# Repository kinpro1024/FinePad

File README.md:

# FinePad (kinpro1024 × ROY21)
### Precision Dual-Axis Macropad
FinePad is a macropad designed with fine pointer control for precision-requiring situations like colour curve modificatioins or timeline scrubbing.
FinePad comes with two independently scrolling Rotary Encoder Knobs for precision X and Y axis control of the Pointer.

This is the version of finepad with no screen. A version with mode toggle and screen is coming soon.

Finepad is built on a Custom PCB.

*This is a concept sketch of the FinePad.*

## Why Fine pointer control
A macropad with dual fine scrolling knobs for X and Y control gives users a level of precision that mice and trackpads struggle to achieve. When working with:
- Colour Curves
- Exposure
- Fine Parameter Sliders
As even small unintended movements with a mouse can lead to inconsistent results in these situations.

**Dedicated knobs allow for smooth, incremental control, making subtle adjustments far more intuitive and repeatable.** Separating X and Y into physical controls also reduces cognitive load, since each axis becomes a deliberate action rather than a coordinated hand movement. This is especially valuable in workflows like:
- Photo Editing
- Colour Grading
- Audio Tuning
Where precision directly impacts output quality. Overall, it transforms delicate adjustments from a frustrating task into a controlled, tactile experience.

## Hardware Overview
FinePad uses a custom PCB as it's base:
- Raspberry Pi Pico handles Firmware.
- Two AS5600 Hall Effect Absolute Encoders.

# FinePad (screenless) was completed on 10/Apr/2026. It is a collaboration between kinpro1024 and ROY21.
# FinePad will get a toggle switch, screen and volume knob in an upcoming update. The full firmware will also come soon.

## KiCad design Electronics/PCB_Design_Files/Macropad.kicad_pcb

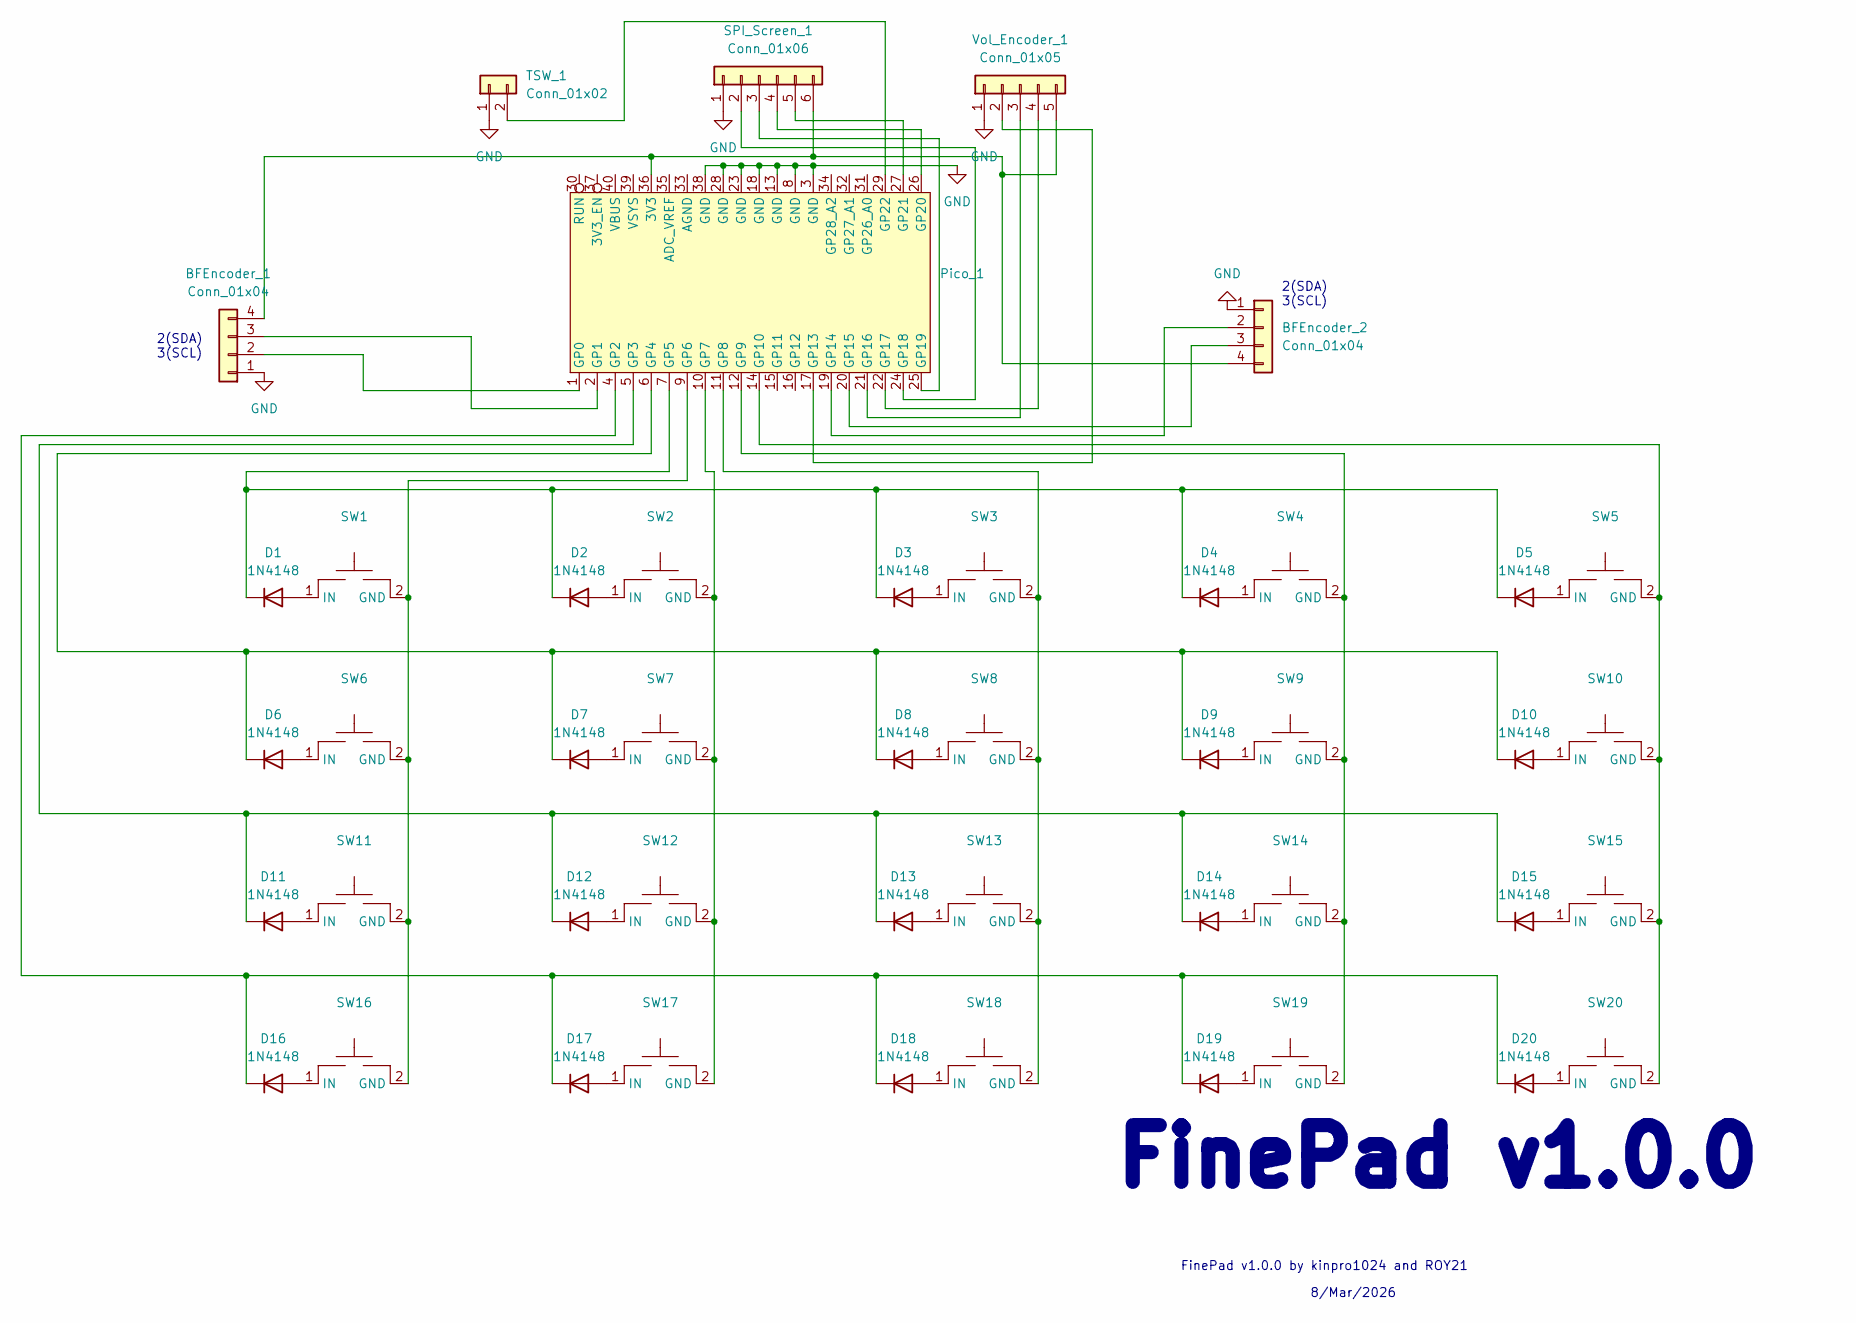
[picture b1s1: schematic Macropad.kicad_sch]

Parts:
BFEncoder_1, BFEncoder_2: Conn_01x04; JST_XH_S4B-XH-A-1_1x04_P2.50mm_Horizontal
D1, D2, D3, D4, D5, D6, D7, D8, D9, D10, D11, D12, D13, D14, D15, D16, D17, D18, D19, D20: 1N4148; D_DO-35_SOD27_P7.62mm_Horizontal
Pico_1: Pico_SMT
SPI_Screen_1: Conn_01x06; JST_XH_S6B-XH-A-1_1x06_P2.50mm_Horizontal
SW1, SW2, SW3, SW4, SW5, SW6, SW7, SW8, SW9, SW10, SW11, SW12, SW13, SW14, SW15, SW16, SW17, SW18, SW19, SW20: Gateron_G_Pro_3
TSW_1: Conn_01x02; JST_XH_S2B-XH-A-1_1x02_P2.50mm_Horizontal
Vol_Encoder_1: Conn_01x05; JST_XH_S5B-XH-A-1_1x05_P2.50mm_Horizontal

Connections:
GND: BFEncoder_1.1, BFEncoder_2.1, Pico_1.3 (GND), Pico_1.8 (GND), Pico_1.13 (GND), Pico_1.18 (GND), Pico_1.23 (GND), Pico_1.28 (GND), Pico_1.38 (GND), SPI_Screen_1.1, TSW_1.1, Vol_Encoder_1.1; also elsewhere on the board
unnamed 1: BFEncoder_1.2, Pico_1.1 (GP0); also elsewhere on the board
unnamed 2: BFEncoder_1.3, Pico_1.2 (GP1); also elsewhere on the board
unnamed 3: BFEncoder_1.4, BFEncoder_2.4, Pico_1.36 (3V3), SPI_Screen_1.6, Vol_Encoder_1.5; also elsewhere on the board
unnamed 4: BFEncoder_2.2, Pico_1.19 (GP14); also elsewhere on the board
unnamed 5: BFEncoder_2.3, Pico_1.20 (GP15); also elsewhere on the board
unnamed: D1.2 (A), SW1.1 (IN)
unnamed 7: D1.1 (K), D2.1 (K), D3.1 (K), D4.1 (K), D5.1 (K), Pico_1.7 (GP5); also elsewhere on the board
unnamed: D2.2 (A), SW2.1 (IN)
unnamed: D3.2 (A), SW3.1 (IN)
unnamed: D4.2 (A), SW4.1 (IN)
unnamed: D5.2 (A), SW5.1 (IN)
unnamed: D6.2 (A), SW6.1 (IN)
unnamed: D7.2 (A), SW7.1 (IN)
unnamed: D8.2 (A), SW8.1 (IN)
unnamed: D9.2 (A), SW9.1 (IN)
unnamed: D10.2 (A), SW10.1 (IN)
unnamed 17: D6.1 (K), D7.1 (K), D8.1 (K), D9.1 (K), D10.1 (K), Pico_1.6 (GP4); also elsewhere on the board
unnamed: D11.2 (A), SW11.1 (IN)
unnamed 19: D11.1 (K), D12.1 (K), D13.1 (K), D14.1 (K), D15.1 (K), Pico_1.5 (GP3); also elsewhere on the board
unnamed: D12.2 (A), SW12.1 (IN)
unnamed: D13.2 (A), SW13.1 (IN)
unnamed: D14.2 (A), SW14.1 (IN)
unnamed: D15.2 (A), SW15.1 (IN)
unnamed: D16.2 (A), SW16.1 (IN)
unnamed 25: D16.1 (K), D17.1 (K), D18.1 (K), D19.1 (K), D20.1 (K), Pico_1.4 (GP2); also elsewhere on the board
unnamed: D17.2 (A), SW17.1 (IN)
unnamed: D18.2 (A), SW18.1 (IN)
unnamed: D19.2 (A), SW19.1 (IN)
unnamed: D20.2 (A), SW20.1 (IN)
unnamed 30: Pico_1.9 (GP6), SW1.2 (GND), SW6.2 (GND), SW11.2 (GND), SW16.2 (GND); also elsewhere on the board
unnamed 31: Pico_1.10 (GP7), SW2.2 (GND), SW7.2 (GND), SW12.2 (GND), SW17.2 (GND); also elsewhere on the board
unnamed 32: Pico_1.11 (GP8), SW3.2 (GND), SW8.2 (GND), SW13.2 (GND), SW18.2 (GND); also elsewhere on the board
unnamed 33: Pico_1.12 (GP9), SW4.2 (GND), SW9.2 (GND), SW14.2 (GND), SW19.2 (GND); also elsewhere on the board
unnamed 34: Pico_1.14 (GP10), SW5.2 (GND), SW10.2 (GND), SW15.2 (GND), SW20.2 (GND); also elsewhere on the board
unnamed 35: Pico_1.17 (GP13), Vol_Encoder_1.2; also elsewhere on the board
unnamed 36: Pico_1.21 (GP16), Vol_Encoder_1.3; also elsewhere on the board
unnamed 37: Pico_1.22 (GP17), Vol_Encoder_1.4; also elsewhere on the board
unnamed 38: Pico_1.24 (GP18), SPI_Screen_1.2; also elsewhere on the board
unnamed 39: Pico_1.25 (GP19), SPI_Screen_1.3; also elsewhere on the board
unnamed 40: Pico_1.26 (GP20), SPI_Screen_1.4; also elsewhere on the board
unnamed 41: Pico_1.27 (GP21), SPI_Screen_1.5; also elsewhere on the board
unnamed 42: Pico_1.29 (GP22), TSW_1.2; also elsewhere on the board

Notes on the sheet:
FinePad v1.0.0 by kinpro1024 and ROY21
8/Mar/2026
2(SDA) 3(SCL)
FinePad v1.0.0

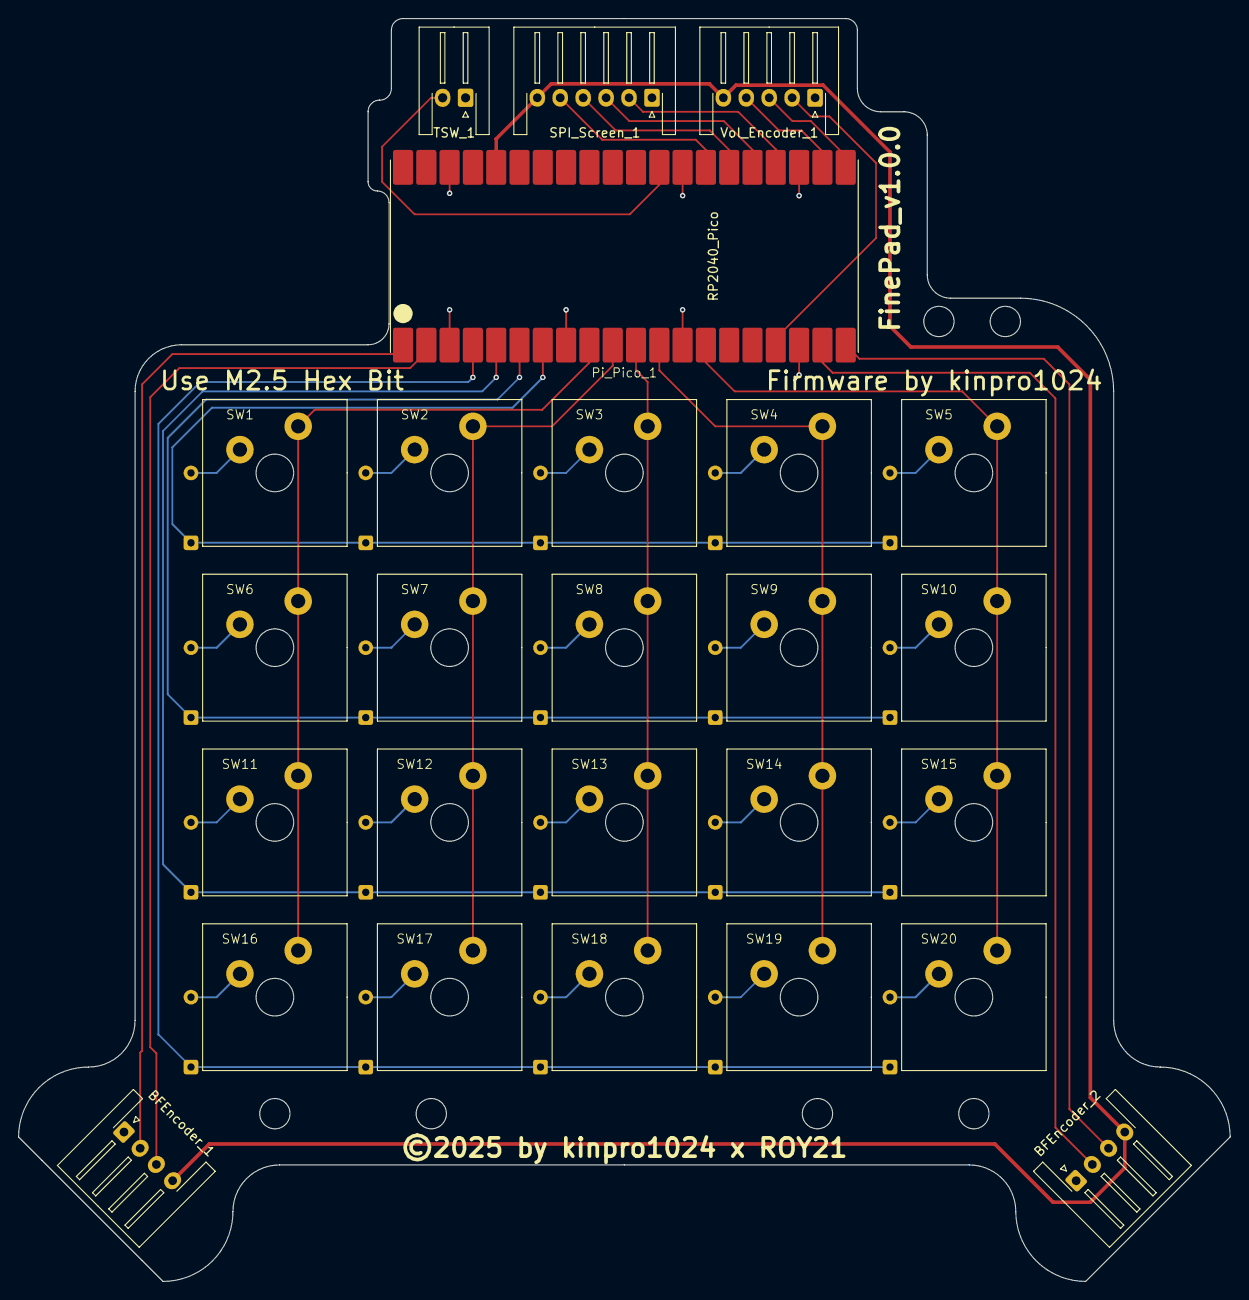
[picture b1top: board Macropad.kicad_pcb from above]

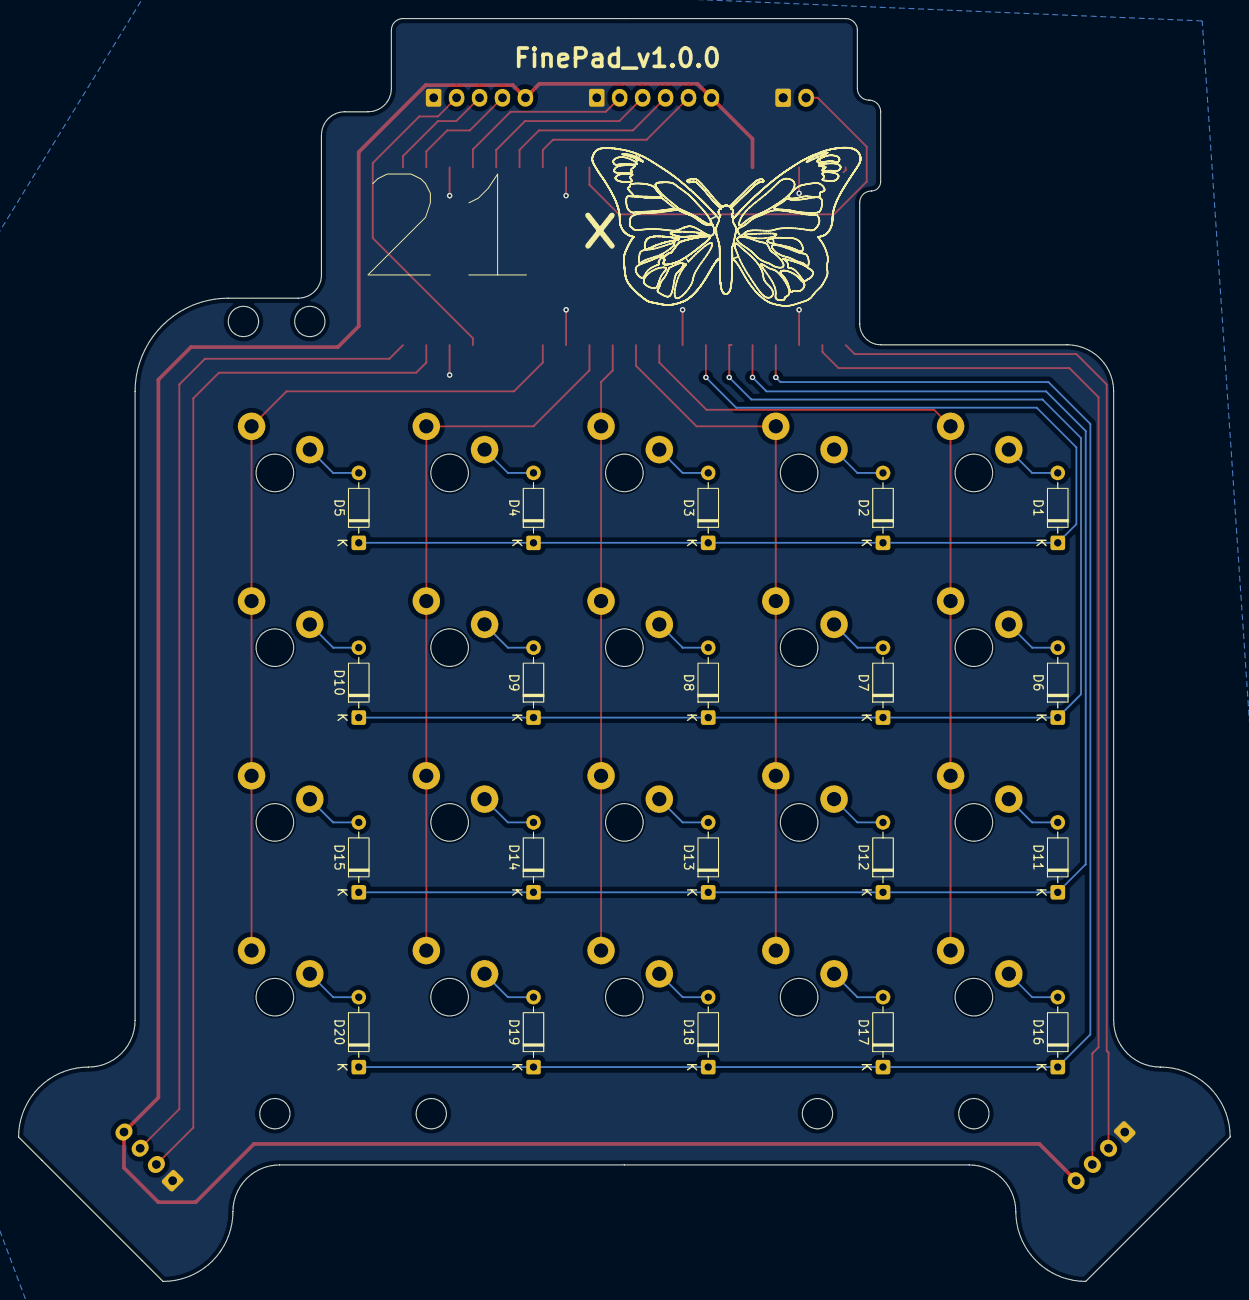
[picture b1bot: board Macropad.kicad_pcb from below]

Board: 2 copper layers, 132.1 x 137.7 mm, 46 parts (20 on the bottom side), 43 nets.

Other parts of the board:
Pi_Pico_1: RP2040_Pico; Pico_SMT

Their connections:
GND: Pi_Pico_1.3 (GND), Pi_Pico_1.8 (GND), Pi_Pico_1.13 (GND), Pi_Pico_1.18 (GND), Pi_Pico_1.23 (GND), Pi_Pico_1.28 (GND), Pi_Pico_1.38 (GND); also elsewhere on the board
unnamed 1: Pi_Pico_1.1 (GP0); also elsewhere on the board
unnamed 2: Pi_Pico_1.2 (GP1); also elsewhere on the board
unnamed 3: Pi_Pico_1.36 (3V3); also elsewhere on the board
unnamed 4: Pi_Pico_1.19 (GP14); also elsewhere on the board
unnamed 5: Pi_Pico_1.20 (GP15); also elsewhere on the board
unnamed 7: Pi_Pico_1.7 (GP5); also elsewhere on the board
unnamed 17: Pi_Pico_1.6 (GP4); also elsewhere on the board
unnamed 19: Pi_Pico_1.5 (GP3); also elsewhere on the board
unnamed 25: Pi_Pico_1.4 (GP2); also elsewhere on the board
unnamed 30: Pi_Pico_1.9 (GP6); also elsewhere on the board
unnamed 31: Pi_Pico_1.10 (GP7); also elsewhere on the board
unnamed 32: Pi_Pico_1.11 (GP8); also elsewhere on the board
unnamed 33: Pi_Pico_1.12 (GP9); also elsewhere on the board
unnamed 34: Pi_Pico_1.14 (GP10); also elsewhere on the board
unnamed 35: Pi_Pico_1.17 (GP13); also elsewhere on the board
unnamed 36: Pi_Pico_1.21 (GP16); also elsewhere on the board
unnamed 37: Pi_Pico_1.22 (GP17); also elsewhere on the board
unnamed 38: Pi_Pico_1.24 (GP18); also elsewhere on the board
unnamed 39: Pi_Pico_1.25 (GP19); also elsewhere on the board
unnamed 40: Pi_Pico_1.26 (GP20); also elsewhere on the board
unnamed 41: Pi_Pico_1.27 (GP21); also elsewhere on the board
unnamed 42: Pi_Pico_1.29 (GP22); also elsewhere on the board

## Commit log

2026-04-01 Init and README
2026-04-01 README Changes
2026-04-01 added Electroics files
2026-04-15 Added Mechanical Files
2026-04-15 Added Current Firmware Files

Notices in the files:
Electronics/PCB_Design_Files/Macropad.kicad_pcb:
©2025 by kinpro1024 x ROY21
